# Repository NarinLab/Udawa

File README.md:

# Udawa 
Halaman projek UDAWA, berisi cetak biru dan dokumentasi lengkap dari perangkat UDAWA. UDAWA adalah sebuah platform instrumentasi pertanian berteknologi Internet of Things yang memungkinkan petani bertani secara terukur dan mengendalikan instrumen pertanian seperti pompa dan mesin dari mana saja melalui Internet dan ponsel pintar.

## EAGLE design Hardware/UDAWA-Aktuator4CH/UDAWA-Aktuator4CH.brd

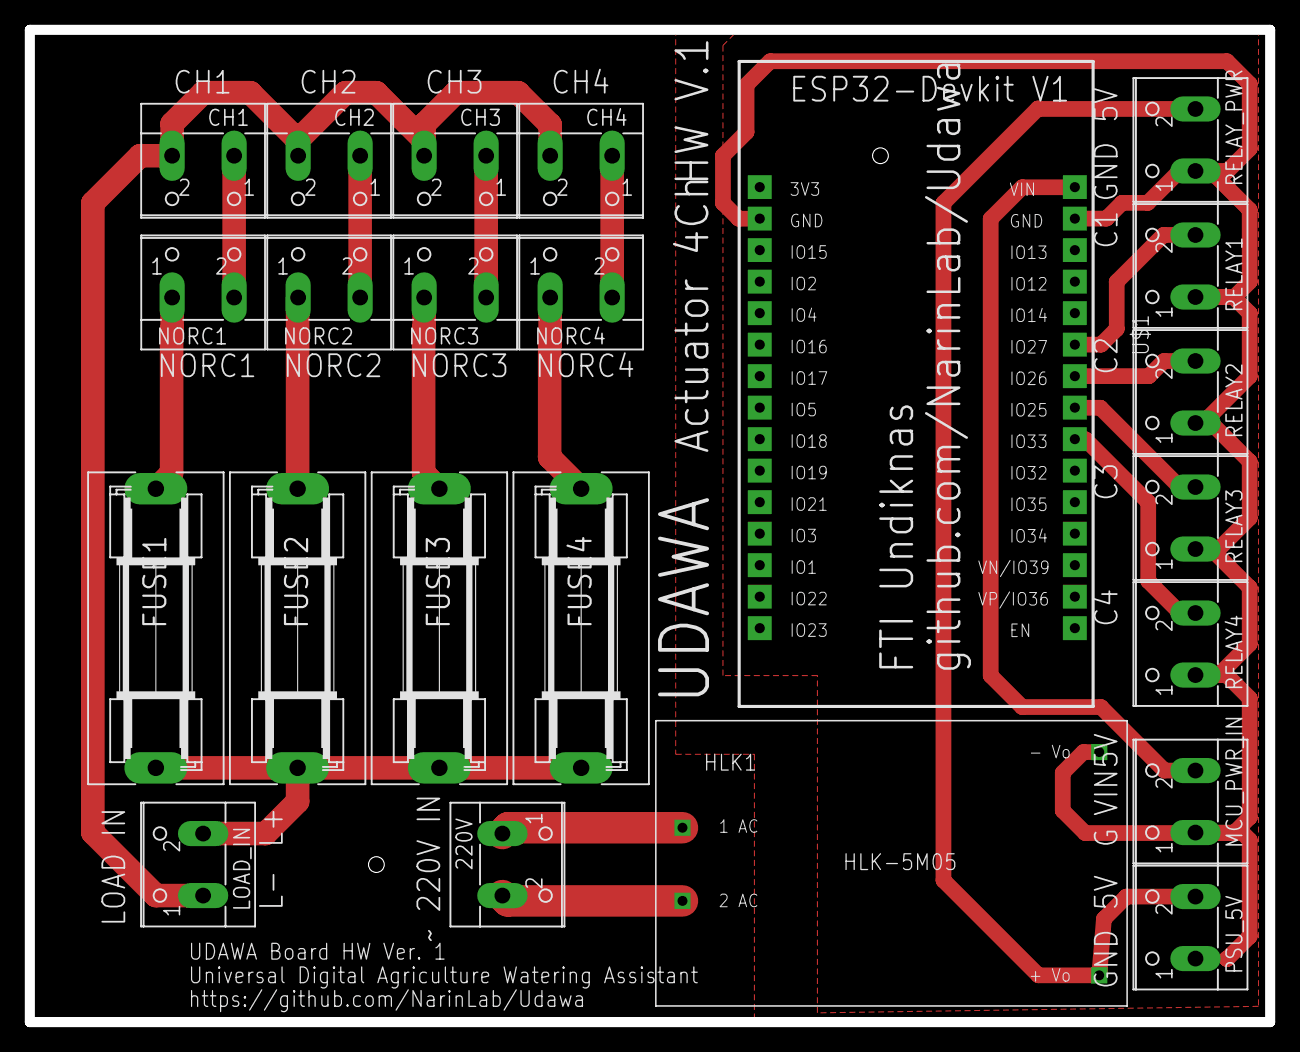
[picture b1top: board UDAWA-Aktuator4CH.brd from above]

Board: 2 copper layers, 100.0 x 80.0 mm, 23 parts (0 on the bottom side), 19 nets.

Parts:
220V: W237-102
CH1, CH2, CH3, CH4: W237-102
FUSE1, FUSE2, FUSE3, FUSE4: SH22,5A
HLK1: 5VDC/5W; HLK-5M05
LOAD_IN: W237-102
MCU_PWR_IN: W237-102
NORC1, NORC2, NORC3, NORC4: W237-102
PSU_5V: W237-102
RELAY1, RELAY2, RELAY3, RELAY4: W237-102
RELAY_PWR: W237-102
U$1: ESP32DEVKITV1; ESP32-DEVKITV1

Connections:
5V: HLK1.4, PSU_5V.2, RELAY_PWR.2
AC1: 220V.2, HLK1.1
AC2: 220V.1, HLK1.2
C1: RELAY1.2, U$1.D27
C2: RELAY2.2, U$1.D26
C3: RELAY3.2, U$1.D25
C4: RELAY4.2, U$1.D33
F1: FUSE1.1, NORC1.1
F2: FUSE2.1, NORC2.1
F3: FUSE3.1, NORC3.1
F4: FUSE4.1, NORC4.1
GND: HLK1.3, MCU_PWR_IN.1, PSU_5V.1, RELAY1.1, RELAY2.1, RELAY3.1, RELAY4.1, RELAY_PWR.1, U$1.GND@1, U$1.GND@2
LOAD+: FUSE1.2, FUSE2.2, FUSE3.2, FUSE4.2, LOAD_IN.2
LOAD-: CH1.2, CH2.2, CH3.2, CH4.2, LOAD_IN.1
RC1: CH1.1, NORC1.2
RC2: CH2.1, NORC2.2
RC3: CH3.1, NORC3.2
RC4: CH4.1, NORC4.2
VIN: MCU_PWR_IN.2, U$1.VIN

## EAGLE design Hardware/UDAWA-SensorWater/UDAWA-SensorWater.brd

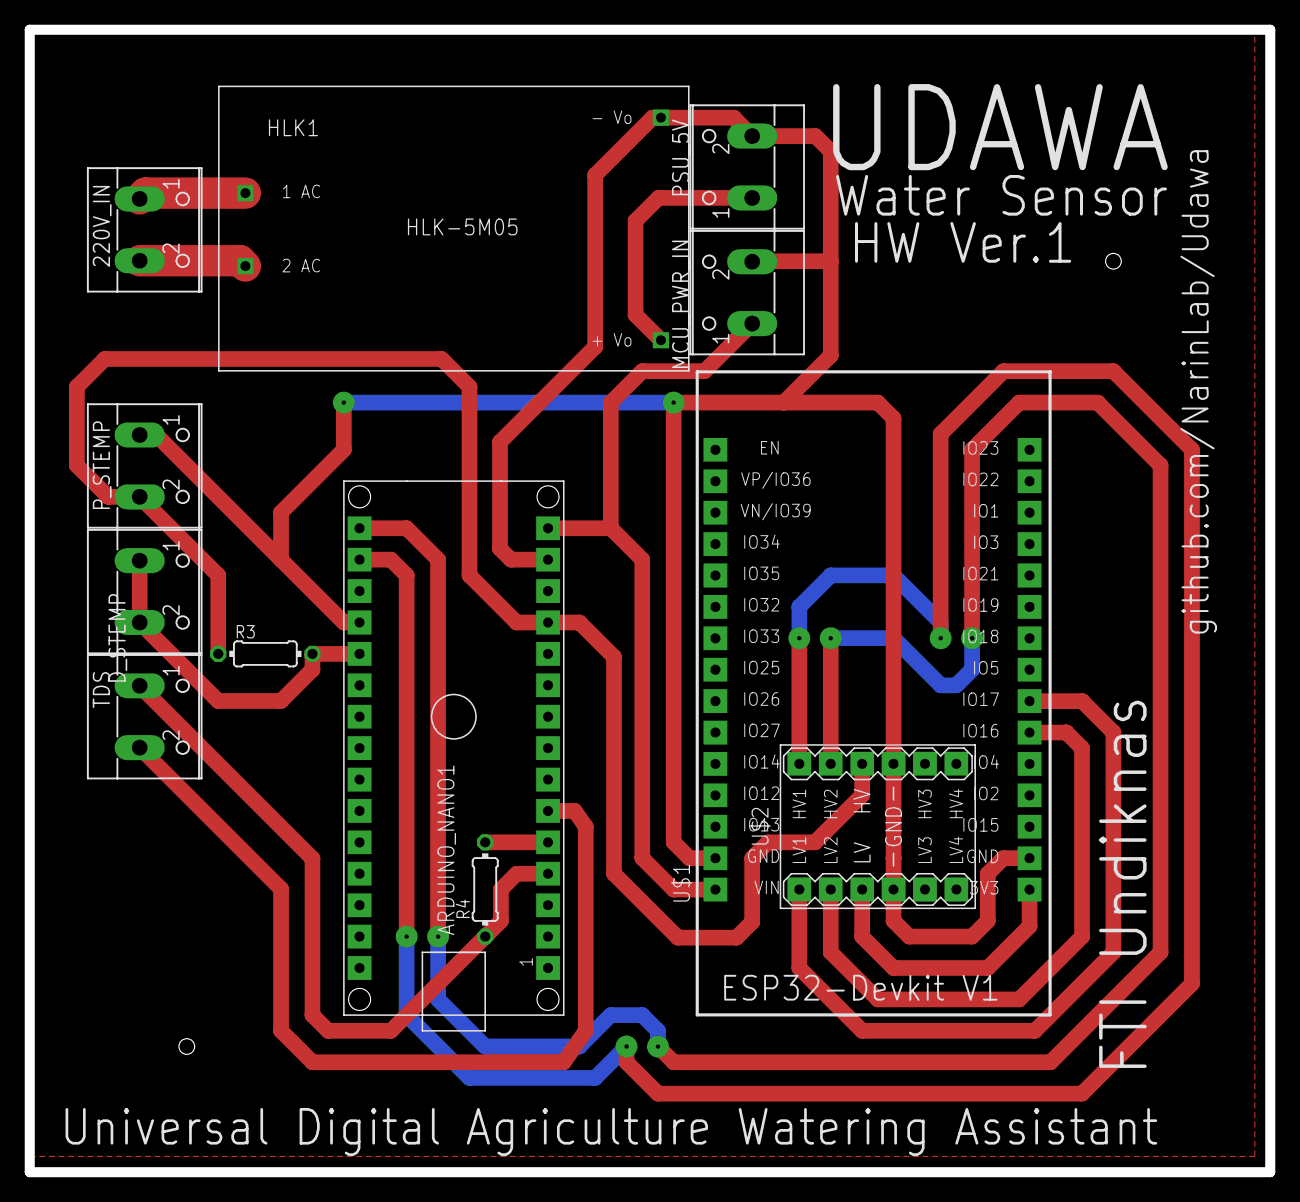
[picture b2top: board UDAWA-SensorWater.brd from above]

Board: 2 copper layers, 100.3 x 92.4 mm, 12 parts (0 on the bottom side), 15 nets.

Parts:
220V_IN: W237-102
ARDUINO_NANO1: ARDUINO_NANO
D_STEMP: W237-102
HLK1: 5VDC/5W; HLK-5M05
MCU_PWR_IN: W237-102
PSU_5V: W237-102
P_STEMP: W237-102
R3: 4.7K; 0204/7
R4: 1K; 0204/7
TDS: W237-102
U$1: ESP32DEVKITV1; ESP32-DEVKITV1
U$2: LEVEL-SHIFTER-4CH

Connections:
3V3: U$1.3V3, U$2.J1.3
5V: HLK1.4, PSU_5V.1
5V_NANO: ARDUINO_NANO1.12, P_STEMP.2, R3.1, U$2.J2.3
A0: ARDUINO_NANO1.4, R4.1, TDS.1
A1: ARDUINO_NANO1.5, R4.2
A2: ARDUINO_NANO1.6, TDS.2
AC1: 220V_IN.2, HLK1.1
AC2: 220V_IN.1, HLK1.2
D2: ARDUINO_NANO1.20, D_STEMP.1, D_STEMP.2, R3.2
GND: ARDUINO_NANO1.14, ARDUINO_NANO1.19, HLK1.3, MCU_PWR_IN.2, PSU_5V.2, P_STEMP.1, U$1.GND@1, U$1.GND@2, U$2.J1.4, U$2.J2.4
HV1: ARDUINO_NANO1.17, U$2.J2.1
HV2: ARDUINO_NANO1.16, U$2.J2.2
LV1: U$1.D17, U$2.J1.1
LV2: U$1.D16, U$2.J1.2
VIN: ARDUINO_NANO1.15, MCU_PWR_IN.1, U$1.VIN

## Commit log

2021-09-07 added eagle hw lib
2021-09-07 Design Pertama board aktuator4CH
2021-09-07 Help reroute
2021-09-09 Added Acuator4CH Wiring Driagrams.net
2021-09-09 added sensorwater diagrams.net
2021-09-09 Initialized Actuator4CH-ESP32
2021-09-10 to do list 6 dan 7
2021-09-10 #3 perbaikan6&7
2021-09-10 #3 to do list 6&7
2021-09-10 #3 to do list 1 sampai 5
2021-09-10 Inisialisasi firmware projek SensorWater-Nano dan menambahkan library yang diperlukan #9
    Inisialisasi firmware untuk projek SensorWater-Nano dengan PlatformIO
2021-09-13 #3 perbaikan to do list 1sampai5
2021-09-13 penambahan komponen Arduino Nano & Logic Level Converter #6
    baru melakukan wiring & belum melakukan routing pada board
    komponen yang belum ditambahkan : Terminal Block, Sensor TDS, DS18B20
2021-09-13 Inisialisasi projek untuk firmware SensorWater-ESP32 dengan PlatformIO (Pio) #8
    library: NTPClient, ArduinoJson, StreamUtils, LittleFS_esp32, TaskManagerIO
2021-09-14 #3 wiring pada mode board dan pastikan penamaan setiap pin dan konektor dibuat dengan jelas dan rapi sesuai diagram.
2021-09-15 Menambahkan Terminal Block untuk koneksi ke Sensor TDS dan Sensor DS18B20 dan Wiring sesuai diagram di gambar #6
    Menambahkan Terminal Block untuk koneksi ke Sensor TDS dan Sensor DS18B20 dan Wiring sesuai diagram di gambar #6
2021-09-20 Routing PCB #6
    Routing PCB
2021-09-27 #3 list 8
    masih belum lengkap wiringnya karena kabelnya sudah mentok dan bakalan numpuk kalau dipaksakan
2021-10-01 Revert "Merge pull request #16 from NarinLab/sensor-water"
    This reverts commit fa909a87a465dd37d6351bcf5a105db5a344029a, reversing
    changes made to da9ed59faa8e6d8399543247dba95a3195e07114.
    Conflict Error Fix
2021-10-01 First Working Design (Act4CH Board)
2021-10-01 First working version of Water Sensor
2021-10-02 PCB Print Ready
2021-10-06 Revisi terminal catu daya. Solar panel support.
2021-10-07 revisi fuse holder ke SH22,5A (Version 1)
2021-10-07 Update esp32 & nano original lib
2021-10-07 Revisi modul original
    Revisi modul original
2021-10-07 Revert "revisi fuse holder ke SH22,5A (Version 1)"
    This reverts commit d673f62cc688c510ac19bdbae74e3cbf1f8eb5bd.
    ada masalah dengan printscale
2021-10-07 Revisi HLK 5M05
2021-10-07 remove brd scm temp file
2021-10-11 Revisi mirroring. Board tidak mirror. Silkscreen mirror.
2021-10-11 gabung file pdf
2021-10-30 git add .
2021-10-30 WIP OtaUpdate
2021-10-30 header fix
2021-10-30 add data folder
2021-10-30 first trial
2021-11-01 checkpoint with mySettings. Runtime untested
2021-11-01 update secret.h-example
2021-11-06 [WIP] Actuator Control
2021-11-06 mySettings.lastConnected
2021-11-06 [WIP] Relay test
2021-11-06 Implemented dutyRuntime()
2021-11-06 Improvement
2021-11-08 [WIP] Implemented MQTT OTA Update
2021-11-12 ch0 to ch1
2021-11-12 firmware 0.0.2
2021-11-12 [WIP] OTA Update
2021-11-12 0.0.3
2021-11-12 Checkpoint Switching
2021-11-12 Checkpoint
2021-11-12 WIP Provisioning
2021-11-12 0.0.5
2021-11-12 UDAWA-Gadadar 0.0.1
2021-11-12 UDAWA-Damodar 0.0.1
2021-11-13 Added Label Design
2021-11-13 update design black
2021-11-13 UDAWA-Damodar 0.0.2
2021-11-13 Added Upload Tools
2021-11-13 bugfix
2021-11-13 0.0.2 + Added Build Tools
2021-11-13 Reverse back to 0.0.1 OTA Major Bug
2021-11-20 added Legacy board actuator support
2021-11-21 rem sec
2021-11-21 ad git ignore
2021-11-22 Revert to 0.0.1
2021-11-24 added ConfigCoMCUSave RPC (0.0.2)
2021-11-24 0.0.3 Added RPC for SynCConfigCoMCU & reboot
2021-11-24 Damodar v0.0.4
2021-11-25 Added reboot RPC to Gadadar
2021-11-25 callbacksSize = 6
2021-11-25 UDAWA Gadadar 0.0.2
2021-11-26 [Bug Fix] glitches on 100% dutyCycle
2021-11-26 [Typo Fix] dutyState[i], Gadadar 0.0.3
2021-12-12 Added DOI for v1.0.0
2021-12-23 legacy-0.0.2
2022-02-18 [WIP] Relay Control Bug
2022-03-18 added vanilla variant (plain code for starterkit)
2022-03-28 removed hardcoded port and broker. [WIP] Vanilla variant
2022-03-28 uint16_t to int
2022-04-01 #define DOCSIZE 1500
2022-04-17 Extensive WIP
2022-04-29 Added various fix in switch
2022-11-13 added rtc
2022-11-14 added relay control by datetime
2022-11-19 added independent control mode
2022-12-03 relay control upgrade
2022-12-16 Added interval control mode

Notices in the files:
parts and their libraries:
diy-modules: Released under the Creative Commons Attribution 4.0 International License: http://creativecommons.org/licenses/by/4.0
